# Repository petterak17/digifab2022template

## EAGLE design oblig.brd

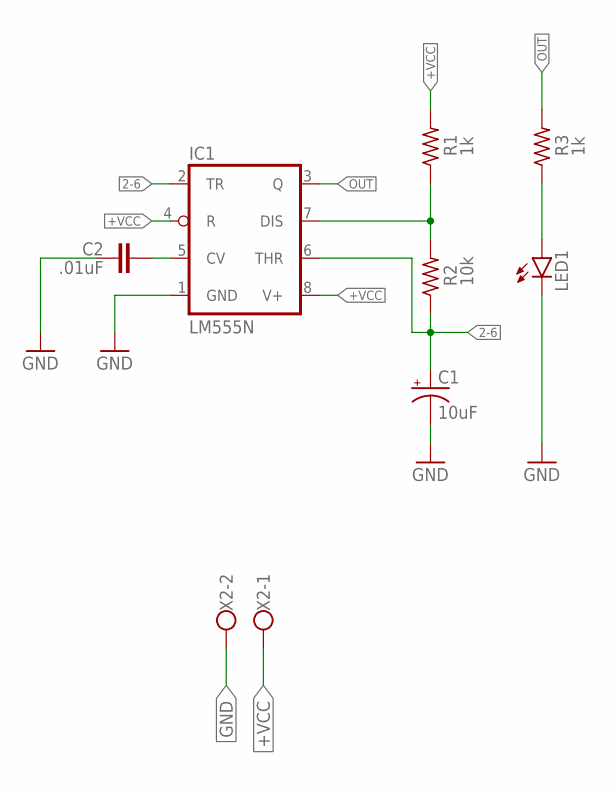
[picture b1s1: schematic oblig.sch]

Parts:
C1: 10uF; E2-5
C2: .01uF; C050-024X044
IC1: LM555N; DIL08
LED1: LED5MM
R1, R3: 1k; 0207/10
R2: 10k; 0207/10
X2: W237-102

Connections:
2-6: C1.+, IC1.2 (TR), IC1.6 (THR), R2.1
+VCC: IC1.4 (R), IC1.8 (V+), R1.2, X2.1
GND: C1.-, C2.1, IC1.1 (GND), LED1.K (C), X2.2
unnamed: IC1.7 (DIS), R1.1, R2.2
unnamed: C2.2, IC1.5 (CV)
unnamed: LED1.A, R3.1
OUT: IC1.3 (Q), R3.2

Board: 2 copper layers, 12 parts (0 on the bottom side), 7 nets, no tracks yet.

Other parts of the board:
U$1, U$2, U$3, U$4: 2,8

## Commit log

2022-09-05 Init
2022-09-05 Michaelify
2023-02-01 test
2023-02-19 bilde til siden
2023-02-19 ny prosjekt
2023-02-19 test
    test
2023-02-19 spaceshipinterface code
    koden til arduino
2023-02-19 Prosjekt 3
2023-03-25 Oblig4
2023-03-25 Prosjekt 4
2023-05-28 Eksamen
2023-05-29 Eksamen
    Fix
2023-05-30 Eksamen
    Endring på nettsiden
